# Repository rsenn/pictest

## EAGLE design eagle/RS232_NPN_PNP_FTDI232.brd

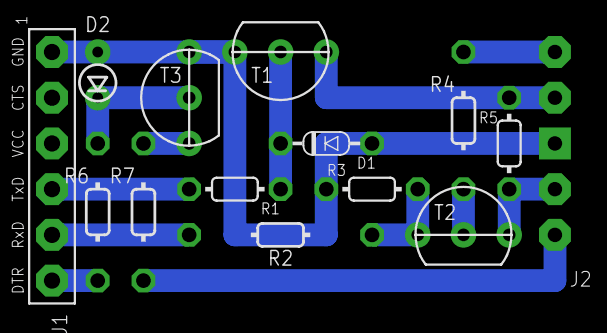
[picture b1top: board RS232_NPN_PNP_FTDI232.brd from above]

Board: 2 copper layers, 14 parts (0 on the bottom side), 13 nets.

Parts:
D1: 1N4148; DO34-5
D2: 1N414834-2,5-A; DO34-2,5-A
J1: FTDI232-BO-R; FTDI232-BO-L
J2: PIC-UART-MCLR
R1: 10kΩ; 0202/5
R2: 1kΩ; 0202/10
R3: 4.7kΩ; 0202/5
R4, R6: 10kΩ; 0202/7-V
R5: 1kΩ; 0202/5-V
R7: 470Ω; 0202/7-V
T1, T3: BC547; TO92-CBE
T2: BC557; TO92-CBE

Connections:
+5V: J2.20, R5.2, T2.E
GND: D1.A, D2.A, J1.GND, J2.19, R3.1, T1.E, T3.E
unnamed: J2.18, R5.1, T1.C
unnamed: D1.C, R1.1, T1.B
unnamed: J1.TXD, R1.2
unnamed: J2.17, R4.1
unnamed: R4.2, T2.B
unnamed: R2.1, R3.2, T2.C
unnamed: J1.RXD, R2.2
unnamed: J2.1, R7.2
unnamed: D2.C, R6.1, T3.B
unnamed: J1.DTR, R6.2
unnamed: R7.1, T3.C

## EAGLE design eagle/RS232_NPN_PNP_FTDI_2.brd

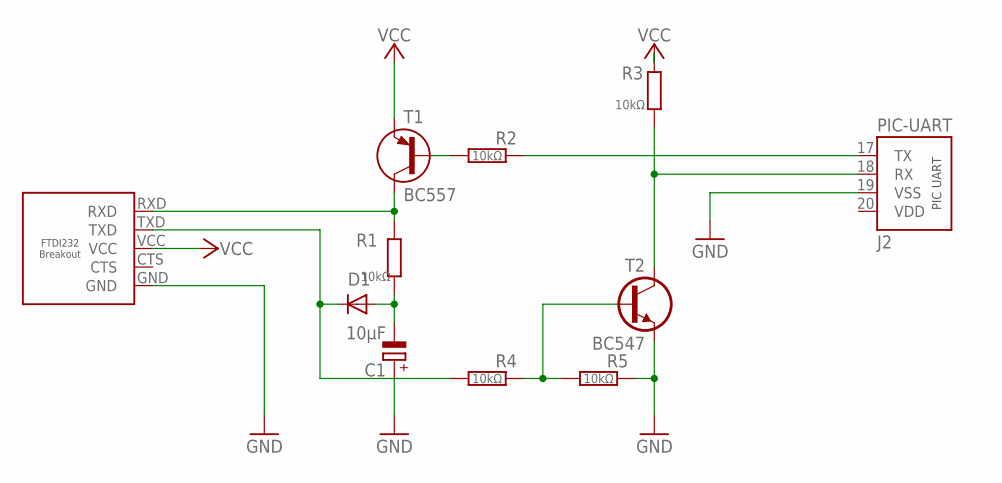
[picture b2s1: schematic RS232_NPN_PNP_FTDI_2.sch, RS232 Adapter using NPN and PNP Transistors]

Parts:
C1: 10μF; E2.5-4/V
D1: 1N4148; DO34-5V
J1: FTDI232-BO-5P-L; FTDI232-BO-5-L
J2: PIC-UART
R1: 10kΩ; 0202/7-V
R2, R3, R4, R5: 10kΩ; 0202/5
T1: BC557; TO92-CBE
T2: BC547; TO92-CBE

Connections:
-12V: C1.-, D1.A, R1.2
GND: C1.+, J1.GND, J2.19 (VSS), R5.1, T2.E
unnamed: R2.2, T1.B
unnamed: R4.1, R5.2, T2.B
RX: J2.18 (RX), R3.1, T2.C
RXD: J1.RXD, R1.1, T1.C
TX: J2.17 (TX), R2.1
TXD: D1.C, J1.TXD, R4.2
VCC: J1.VCC, R3.2, T1.E

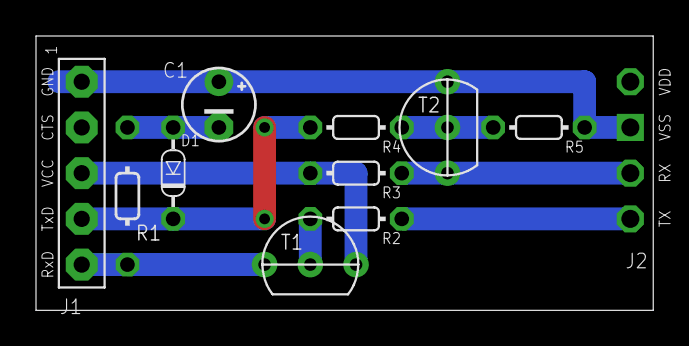
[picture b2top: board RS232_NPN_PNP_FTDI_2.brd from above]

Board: 2 copper layers, 34.3 x 15.2 mm, 11 parts (0 on the bottom side), 9 nets.

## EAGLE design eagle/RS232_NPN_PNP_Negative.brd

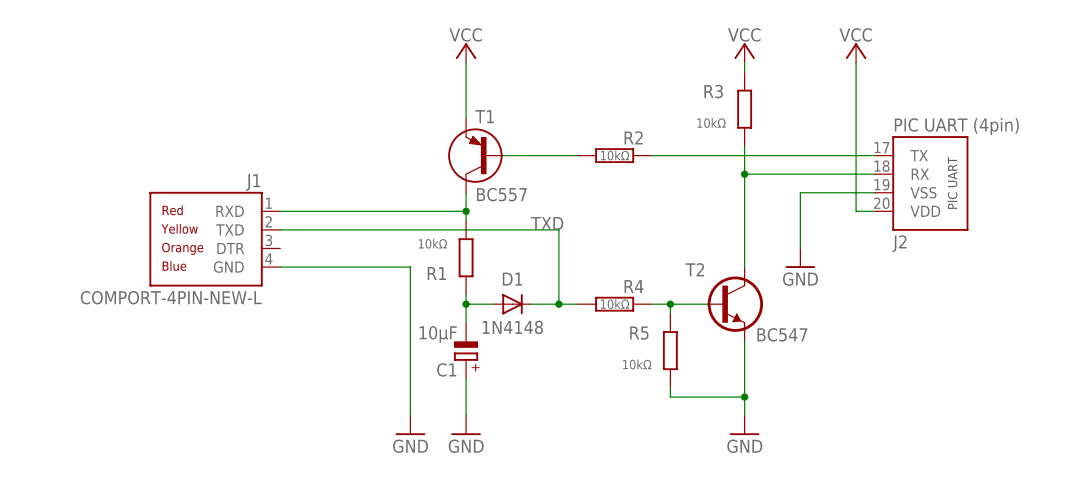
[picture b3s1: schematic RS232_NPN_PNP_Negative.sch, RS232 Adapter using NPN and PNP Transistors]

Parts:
C1: 10μF; E2,5-3
D1: 1N4148; DO34-5
J1: COMPORT-4PIN-NEW-L; RS232-4PIN-NEW-L
J2: PIC UART (4pin); PIC-UART
R1, R4, R5: 10kΩ; 0202/7
R2: 10kΩ; 0202/10-V
R3: 10kΩ; 0202/7-V
T1: BC557; TO92-CBE
T2: BC547; TO92-CBE

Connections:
-12V: C1.-, D1.A, R1.1
GND: C1.+, J1.4 (GND), J2.19 (VSS), R5.2, T2.E
unnamed: R2.2, T1.B
unnamed: R4.1, R5.1, T2.B
RX: J2.18 (RX), R3.1, T2.C
RXD: J1.1 (RXD), R1.2, T1.C
TX: J2.17 (TX), R2.1
TXD: D1.C, J1.2 (TXD), R4.2
VCC: J2.20 (VDD), R3.2, T1.E

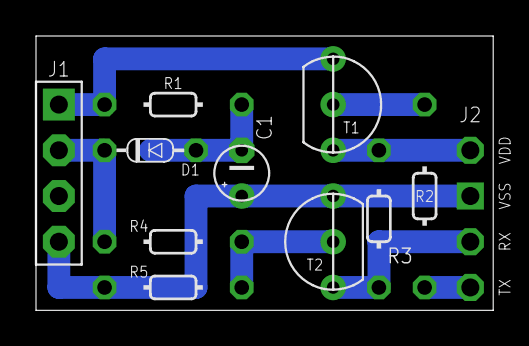
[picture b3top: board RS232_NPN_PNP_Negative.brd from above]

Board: 2 copper layers, 25.4 x 15.2 mm, 11 parts (0 on the bottom side), 9 nets.

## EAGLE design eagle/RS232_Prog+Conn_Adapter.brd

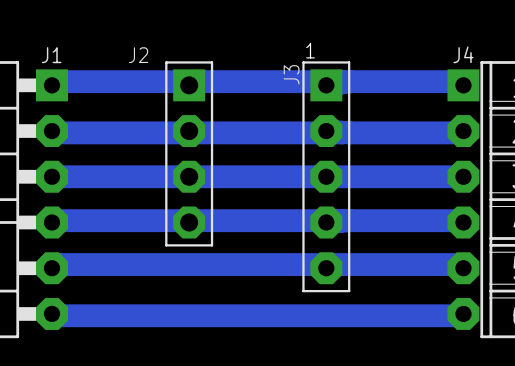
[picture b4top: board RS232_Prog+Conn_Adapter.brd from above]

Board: 2 copper layers, 4 parts (0 on the bottom side), 6 nets.

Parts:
J1: COMPORT-6PIN-NEW-6P-NEW-90-L; RS232-6PIN-NEW-90-L
J2: COMPORT-4PIN-NEW-L; RS232-4PIN-NEW-L
J3: CONN-5P; CONN-5P-N
J4: COMPORT-6PIN-NEW-6P-FEM-90; CONN-6P-FEM-90

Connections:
CTS: J1.CTS, J4.6
DTR: J1.DTR, J2.3, J3.3, J4.3
GND: J1.GND, J2.4, J3.4, J4.4
RTS: J1.RTS, J3.5, J4.5
RXD: J1.RXD, J2.1, J3.1, J4.1
TXD: J1.TXD, J2.2, J3.2, J4.2

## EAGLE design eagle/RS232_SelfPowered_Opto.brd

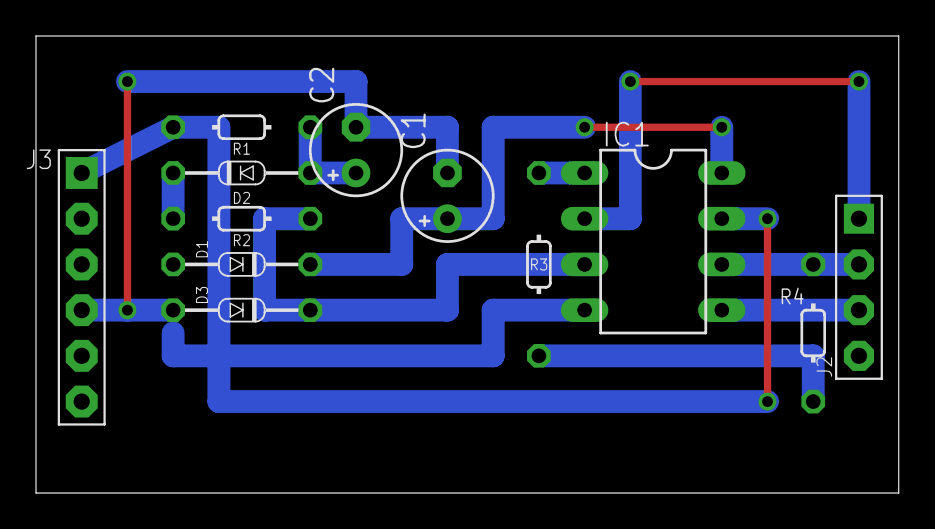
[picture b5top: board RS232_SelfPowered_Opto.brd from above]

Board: 2 copper layers, 47.9 x 25.4 mm, 12 parts (0 on the bottom side), 12 nets.

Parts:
C1, C2: 47u; E2,5-5
D1, D3: 1N914; DO34-7V
D2: 1N914; DO34-7
IC1: ACPL-827; DIL08
J2: PIC-UART-4P; CONN-4P
J3: COMPORT-6PIN-NEW; RS232-6PIN-NEW
R1: 680Ω; 0202/7
R2: 1kΩ; 0202/7
R3: 470Ω; 0202/10-V
R4: 1kΩ; 0202/7-V

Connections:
+5V: J2.4, R3.2, R4.2
DGND: IC1.5, J2.3
DTR: D1.A, J3.3
GND: C1.-, C2.-, D3.A, IC1.4, J3.4
unnamed: C1.+, D1.C, IC1.8
unnamed: IC1.1, R3.1
unnamed: IC1.2, J2.1
unnamed: IC1.6, J2.2, R4.1
unnamed: D3.C, IC1.3, R2.2
unnamed: C2.+, D2.A, R1.2
RXD: IC1.7, J3.1, R1.1
TXD: D2.C, J3.2, R2.1
